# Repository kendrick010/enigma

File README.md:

# enigma

A 65% through-hole keyboard inspired by the Discipline V2 and Nibble keyboard.

The keyboard is flashed using QMK Toolbox.

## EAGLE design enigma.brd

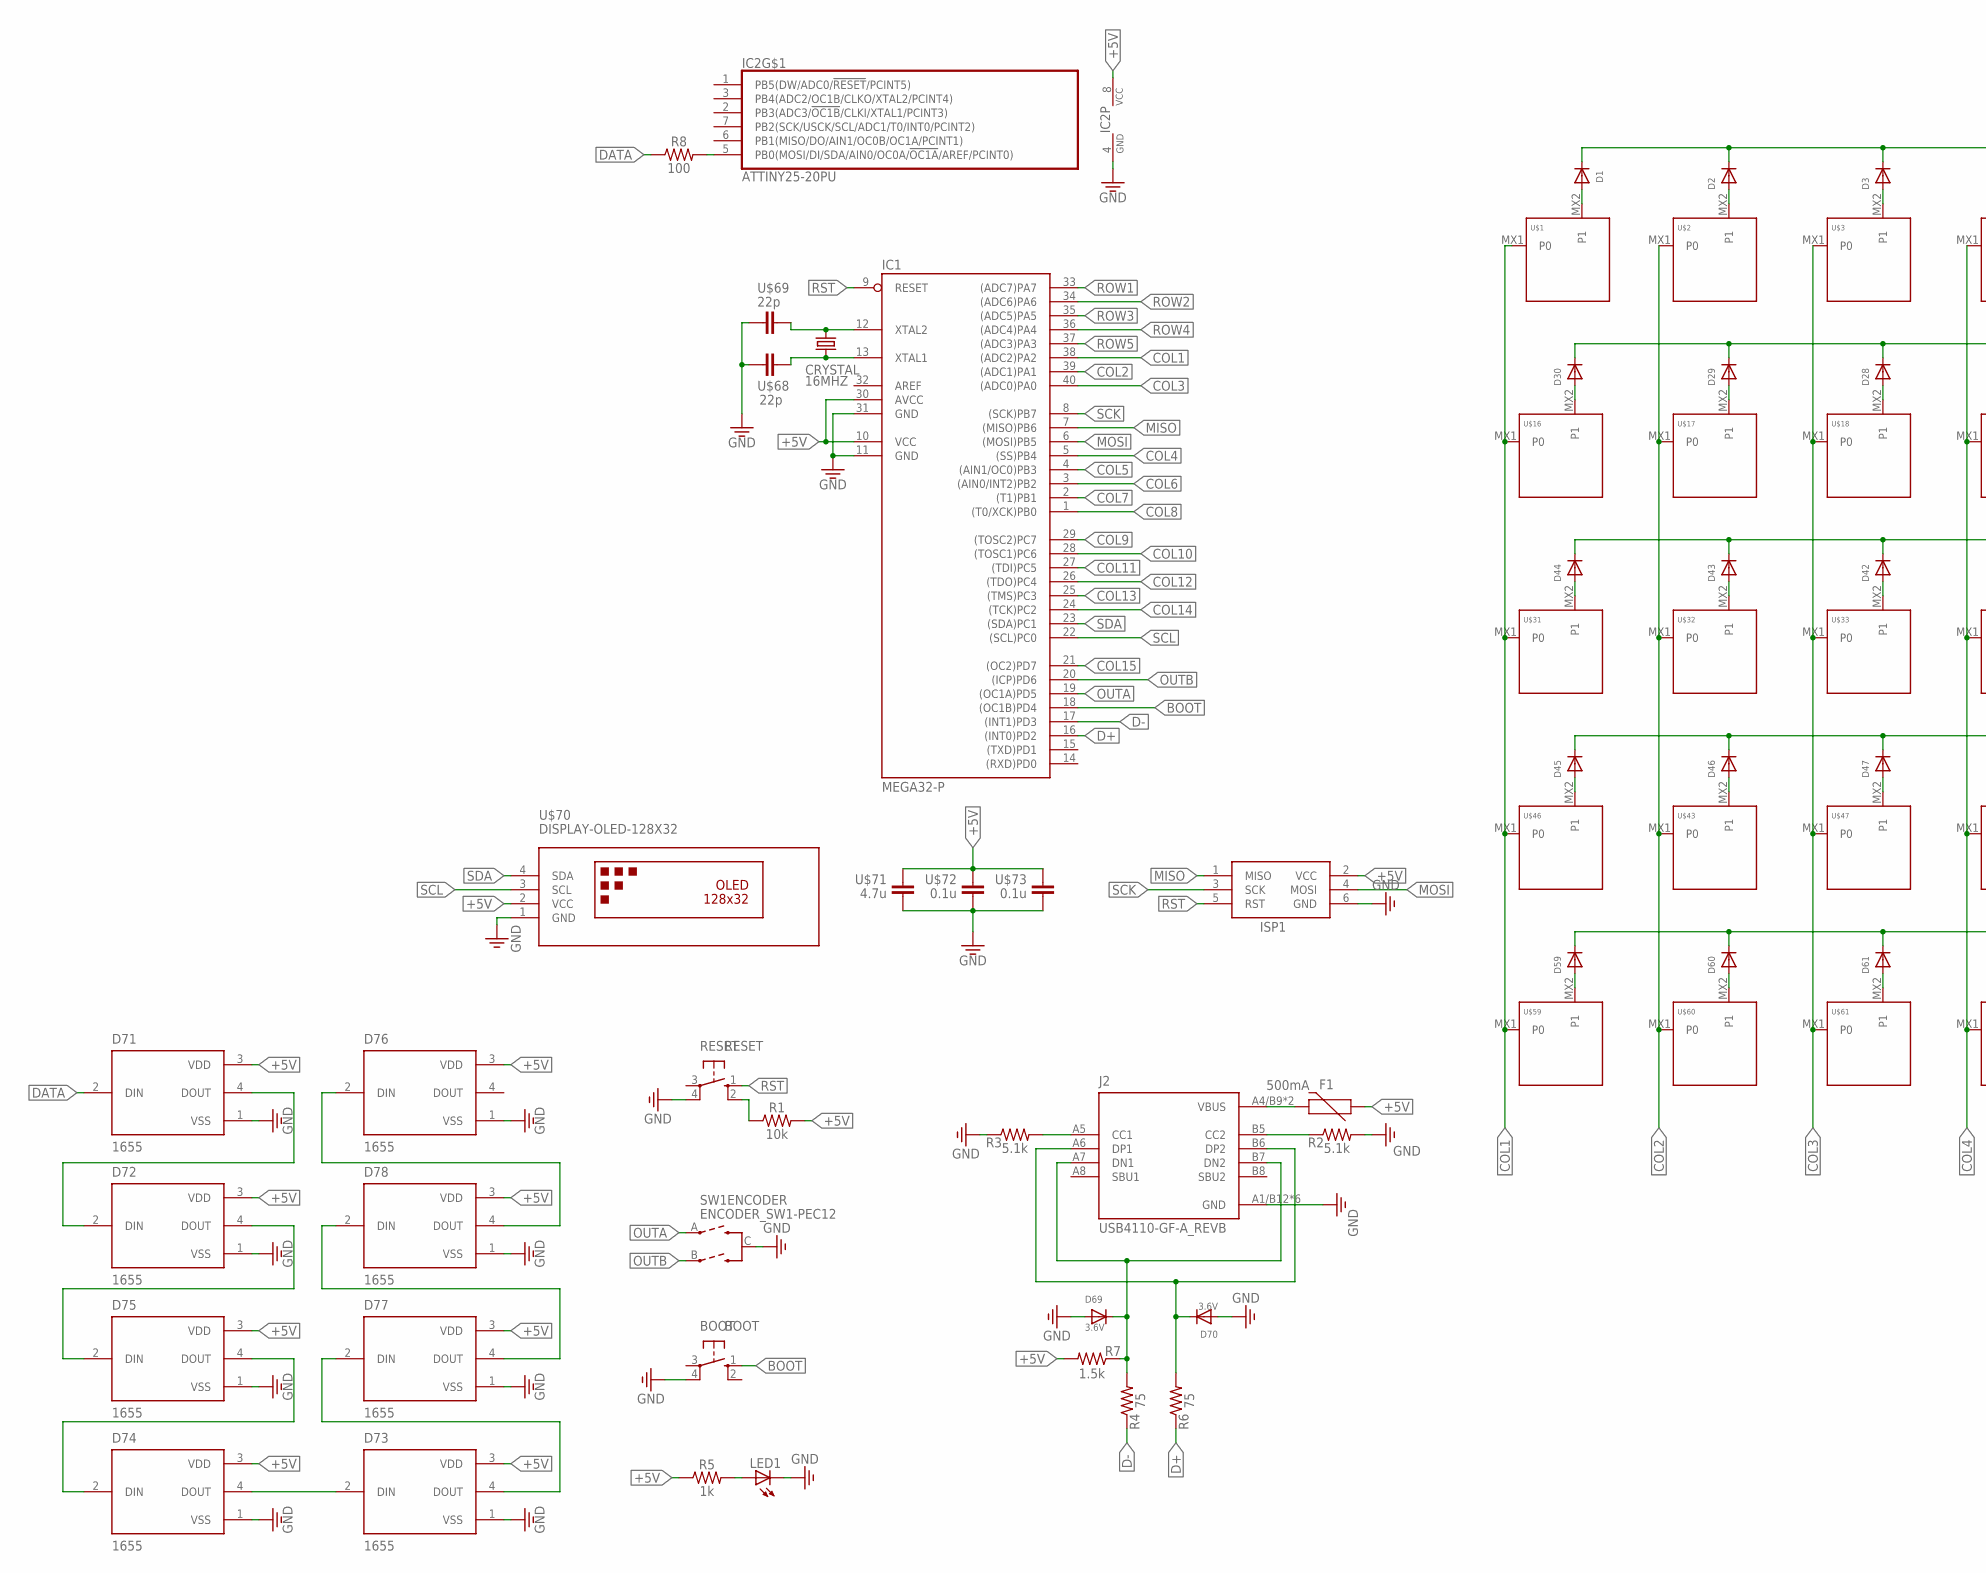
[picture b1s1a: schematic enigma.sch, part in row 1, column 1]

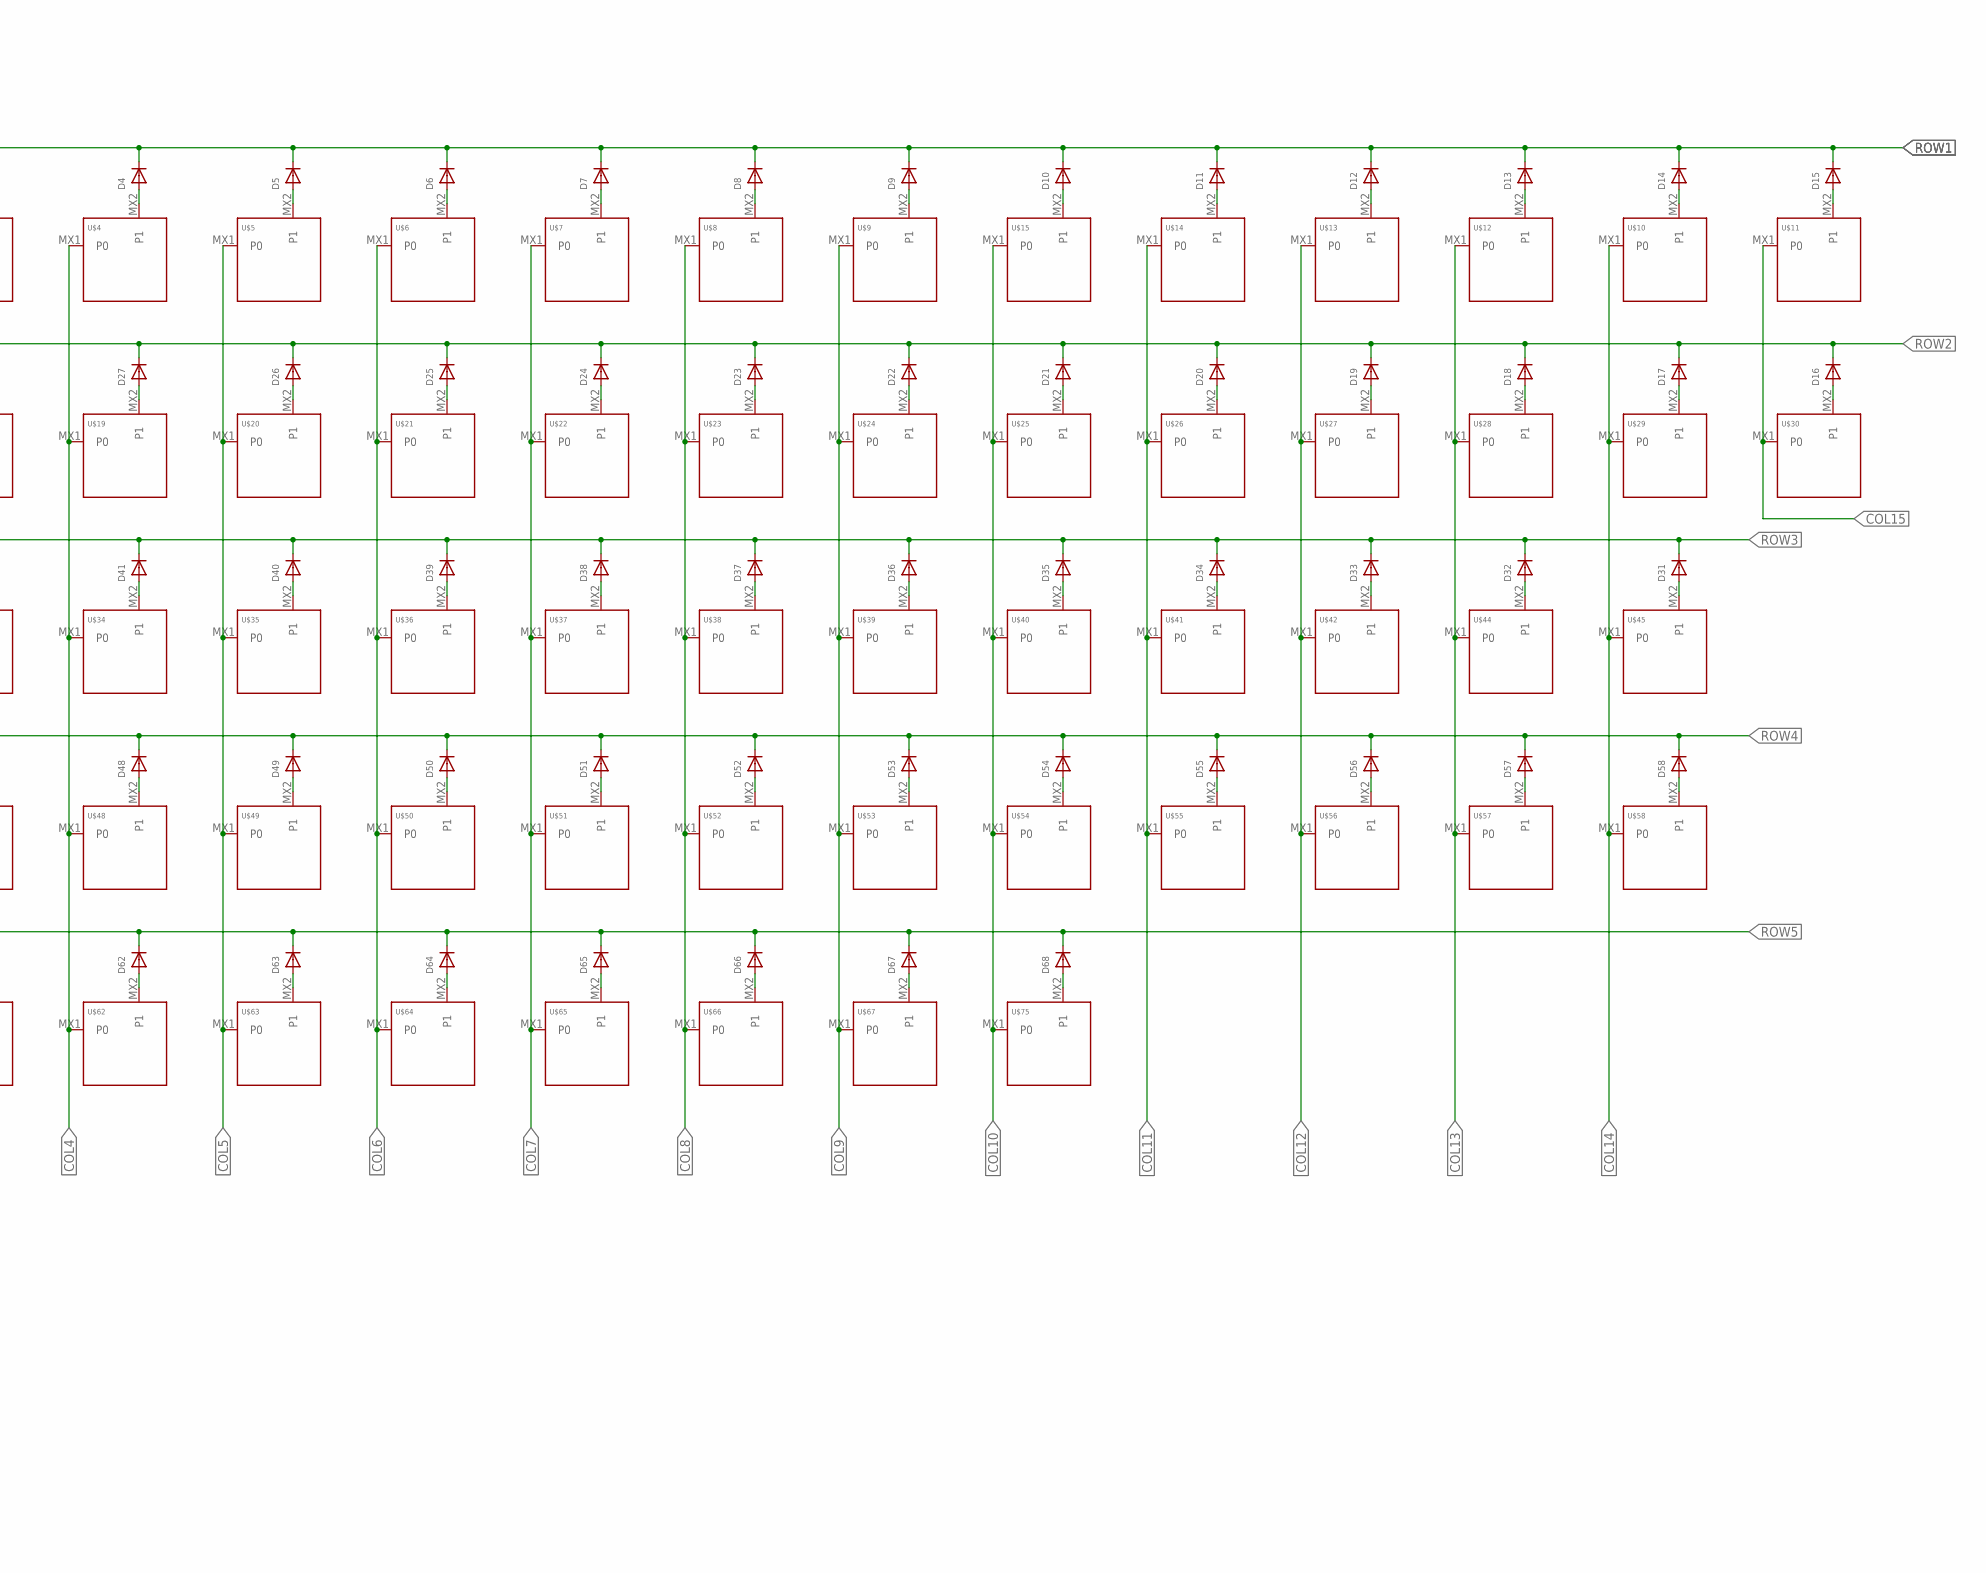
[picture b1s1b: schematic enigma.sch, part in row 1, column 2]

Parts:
BOOT: BOOT; B3F-10XX
CRYSTAL: 16MHZ; HC49U-V
D1, D2, D3, D4, D5, D6, D7, D8, D9, D10, D11, D12, D13, D14, D15, D16, D17, D18, D19, D20, D21, D22, D23, D24, D25, D26, D27, D28, D29, D30, D31, D32, D33, D34, D35, D36, D37, D38, D39, D40, D41, D42, D43, D44, D45, D46, D47, D48, D49, D50, D51, D52, D53, D54, D55, D56, D57, D58, D59, D60, D61, D62, D63, D64, D65, D66, D67, D68: DIODEDO-1N4148; DO-1N4148
D69, D70: 3.6V; DO-1N4148
D71, D72, D73, D74, D75, D76, D77, D78: 1655; LED_1655
F1: 500mA; PTH
IC1: MEGA32-P; DIL40
IC2: ATTINY25-20PU; DIL08
ISP1: AVRISP-6; AVRISP
J2: USB4110-GF-A_REVB; GCT_USB4110-GF-A_REVB
LED1: LED5MM
R1: 10k; AXIAL-0.3
R2, R3: 5.1k; AXIAL-0.3
R4, R6: 75; AXIAL-0.3
R5: 1k; AXIAL-0.3
R7: 1.5k; AXIAL-0.3
R8: 100; AXIAL-0.3
RESET: RESET; B3F-10XX
SW1: ENCODER_SW1-PEC12; PEC12_INCREMENTAL_ENCODER
U$1, U$2, U$3, U$4, U$5, U$6, U$7, U$8, U$9, U$11, U$12, U$13, U$14, U$15, U$16, U$17, U$18, U$19, U$20, U$21, U$22, U$23, U$24, U$25, U$26, U$27, U$28, U$29, U$30, U$31, U$32, U$33, U$34, U$35, U$36, U$37, U$38, U$39, U$40, U$41, U$42, U$43, U$45, U$47, U$48, U$49, U$50, U$51, U$52, U$53, U$54, U$55, U$56, U$57, U$58, U$59, U$60, U$61, U$63, U$64, U$65, U$66, U$67, U$75: KEYSWITCH-PLAIN-MXHSPCB-1U; MXHSPCB-1U
U$10: KEYSWITCH-PLAIN-MXHSPCB-2U; MXHSPCB-2U
U$44, U$46: KEYSWITCH-PLAIN-MXHSPCB-2U-FLIPPED; MXHSPCB-2U-FLIPPED
U$62: KEYSWITCH-PLAIN-MXHSPCB-6.25U-FLIPPED; MXHSPCB-6.25U-FLIPPED
U$68, U$69: 22p; CAP-TH
U$70: DISPLAY-OLED-128X32
U$71: 4.7u; CAP-TH
U$72, U$73: 0.1u; CAP-TH

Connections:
3.3V: BOOT.4 (P1), D69.A, D70.A, D71.1 (VSS), D72.1 (VSS), D73.1 (VSS), D74.1 (VSS), D75.1 (VSS), D76.1 (VSS), D77.1 (VSS), D78.1 (VSS), IC1.11 (GND), IC1.31 (GND), IC2.4 (GND), ISP1.6 (GND), J2.A1/B12 (GND), J2.B1/A12 (GND), J2.S1 (GND), J2.S2 (GND), J2.S3 (GND), J2.S4 (GND), LED1.K (C), R2.P$2 (2), R3.P$1 (1), RESET.4 (P1), SW1.C, U$68.2, U$69.1, U$70.1 (GND), U$71.1, U$72.1, U$73.1
+5V: D71.3 (VDD), D72.3 (VDD), D73.3 (VDD), D74.3 (VDD), D75.3 (VDD), D76.3 (VDD), D77.3 (VDD), D78.3 (VDD), F1.P$1 (1), IC1.10 (VCC), IC1.30 (AVCC), IC2.8 (VCC), ISP1.2 (VCC), R1.P$2 (2), R5.P$1 (1), R7.P$2 (2), U$70.2 (VCC), U$71.2, U$72.2, U$73.2
BOOT: BOOT.1 (S), IC1.18 ((OC1B)PD4)
COL1: IC1.38 ((ADC2)PA2), U$1.MX1 (P0), U$16.MX1 (P0), U$31.MX1 (P0), U$46.MX1 (P0), U$59.MX1 (P0)
COL2: IC1.39 ((ADC1)PA1), U$2.MX1 (P0), U$17.MX1 (P0), U$32.MX1 (P0), U$43.MX1 (P0), U$60.MX1 (P0)
COL3: IC1.40 ((ADC0)PA0), U$3.MX1 (P0), U$18.MX1 (P0), U$33.MX1 (P0), U$47.MX1 (P0), U$61.MX1 (P0)
COL4: IC1.5 ((SS)PB4), U$4.MX1 (P0), U$19.MX1 (P0), U$34.MX1 (P0), U$48.MX1 (P0), U$62.MX1 (P0)
COL5: IC1.4 ((AIN1/OC0)PB3), U$5.MX1 (P0), U$20.MX1 (P0), U$35.MX1 (P0), U$49.MX1 (P0), U$63.MX1 (P0)
COL6: IC1.3 ((AIN0/INT2)PB2), U$6.MX1 (P0), U$21.MX1 (P0), U$36.MX1 (P0), U$50.MX1 (P0), U$64.MX1 (P0)
COL7: IC1.2 ((T1)PB1), U$7.MX1 (P0), U$22.MX1 (P0), U$37.MX1 (P0), U$51.MX1 (P0), U$65.MX1 (P0)
COL8: IC1.1 ((T0/XCK)PB0), U$8.MX1 (P0), U$23.MX1 (P0), U$38.MX1 (P0), U$52.MX1 (P0), U$66.MX1 (P0)
COL9: IC1.29 ((TOSC2)PC7), U$9.MX1 (P0), U$24.MX1 (P0), U$39.MX1 (P0), U$53.MX1 (P0), U$67.MX1 (P0)
COL10: IC1.28 ((TOSC1)PC6), U$15.MX1 (P0), U$25.MX1 (P0), U$40.MX1 (P0), U$54.MX1 (P0), U$75.MX1 (P0)
COL11: IC1.27 ((TDI)PC5), U$14.MX1 (P0), U$26.MX1 (P0), U$41.MX1 (P0), U$55.MX1 (P0)
COL12: IC1.26 ((TDO)PC4), U$13.MX1 (P0), U$27.MX1 (P0), U$42.MX1 (P0), U$56.MX1 (P0)
COL13: IC1.25 ((TMS)PC3), U$12.MX1 (P0), U$28.MX1 (P0), U$44.MX1 (P0), U$57.MX1 (P0)
COL14: IC1.24 ((TCK)PC2), U$10.MX1 (P0), U$29.MX1 (P0), U$45.MX1 (P0), U$58.MX1 (P0)
COL15: IC1.21 ((OC2)PD7), U$11.MX1 (P0), U$30.MX1 (P0)
D+: IC1.16 ((INT0)PD2), R6.P$1 (1)
D-: IC1.17 ((INT1)PD3), R4.P$1 (1)
DATA: D71.2 (DIN), R8.P$1 (1)
MISO: IC1.7 ((MISO)PB6), ISP1.1 (MISO)
MOSI: IC1.6 ((MOSI)PB5), ISP1.4 (MOSI)
unnamed: D1.A, U$1.MX2 (P1)
unnamed: D2.A, U$2.MX2 (P1)
unnamed: D3.A, U$3.MX2 (P1)
unnamed: D4.A, U$4.MX2 (P1)
unnamed: D5.A, U$5.MX2 (P1)
unnamed: D6.A, U$6.MX2 (P1)
unnamed: D7.A, U$7.MX2 (P1)
unnamed: D8.A, U$8.MX2 (P1)
unnamed: D9.A, U$9.MX2 (P1)
unnamed: D10.A, U$15.MX2 (P1)
unnamed: D11.A, U$14.MX2 (P1)
unnamed: D12.A, U$13.MX2 (P1)
unnamed: D13.A, U$12.MX2 (P1)
unnamed: D14.A, U$10.MX2 (P1)
unnamed: D15.A, U$11.MX2 (P1)
unnamed: D30.A, U$16.MX2 (P1)
unnamed: D29.A, U$17.MX2 (P1)
unnamed: D28.A, U$18.MX2 (P1)
unnamed: D27.A, U$19.MX2 (P1)
unnamed: D26.A, U$20.MX2 (P1)
unnamed: D25.A, U$21.MX2 (P1)
unnamed: D24.A, U$22.MX2 (P1)
unnamed: D23.A, U$23.MX2 (P1)
unnamed: D22.A, U$24.MX2 (P1)
unnamed: D21.A, U$25.MX2 (P1)
unnamed: D20.A, U$26.MX2 (P1)
unnamed: D19.A, U$27.MX2 (P1)
unnamed: D18.A, U$28.MX2 (P1)
unnamed: D17.A, U$29.MX2 (P1)
unnamed: D16.A, U$30.MX2 (P1)
unnamed: D44.A, U$31.MX2 (P1)
unnamed: D43.A, U$32.MX2 (P1)
unnamed: D42.A, U$33.MX2 (P1)
unnamed: D41.A, U$34.MX2 (P1)
unnamed: D40.A, U$35.MX2 (P1)
unnamed: D39.A, U$36.MX2 (P1)
unnamed: D38.A, U$37.MX2 (P1)
unnamed: D37.A, U$38.MX2 (P1)
unnamed: D36.A, U$39.MX2 (P1)
unnamed: D35.A, U$40.MX2 (P1)
unnamed: D34.A, U$41.MX2 (P1)
unnamed: D33.A, U$42.MX2 (P1)
unnamed: D32.A, U$44.MX2 (P1)
unnamed: D31.A, U$45.MX2 (P1)
unnamed: D45.A, U$46.MX2 (P1)
unnamed: D46.A, U$43.MX2 (P1)
unnamed: D47.A, U$47.MX2 (P1)
unnamed: D48.A, U$48.MX2 (P1)
unnamed: D49.A, U$49.MX2 (P1)
unnamed: D50.A, U$50.MX2 (P1)
unnamed: D51.A, U$51.MX2 (P1)
unnamed: D52.A, U$52.MX2 (P1)
unnamed: D53.A, U$53.MX2 (P1)
unnamed: D54.A, U$54.MX2 (P1)
unnamed: D55.A, U$55.MX2 (P1)
unnamed: D56.A, U$56.MX2 (P1)
unnamed: D57.A, U$57.MX2 (P1)
unnamed: D58.A, U$58.MX2 (P1)
unnamed: D67.A, U$67.MX2 (P1)
unnamed: D66.A, U$66.MX2 (P1)
unnamed: D65.A, U$65.MX2 (P1)
unnamed: D64.A, U$64.MX2 (P1)
unnamed: D63.A, U$63.MX2 (P1)
unnamed: D62.A, U$62.MX2 (P1)
unnamed: D61.A, U$61.MX2 (P1)
unnamed: D60.A, U$60.MX2 (P1)
unnamed: D68.A, U$75.MX2 (P1)
unnamed: CRYSTAL.1, IC1.12 (XTAL2), U$69.2
unnamed: CRYSTAL.2, IC1.13 (XTAL1), U$68.1
unnamed: D59.A, U$59.MX2 (P1)
unnamed: F1.P$2 (2), J2.A4/B9 (VBUS), J2.B4/A9 (VBUS)
unnamed: J2.B5 (CC2), R2.P$1 (1)
unnamed: J2.A5 (CC1), R3.P$2 (2)
unnamed: D69.C, J2.A7 (DN1), J2.B7 (DN2), R4.P$2 (2), R7.P$1 (1)
unnamed: LED1.A, R5.P$2 (2)
unnamed: R1.P$1 (1), RESET.2 (S1)
unnamed: IC2.5 (PB0(MOSI/DI/SDA/AIN0/OC0A/!OC1A!/AREF/P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), R8.P$2 (2)
unnamed: D71.4 (DOUT), D72.2 (DIN)
unnamed: D70.C, J2.A6 (DP1), J2.B6 (DP2), R6.P$2 (2)
unnamed: D72.4 (DOUT), D75.2 (DIN)
unnamed: D74.2 (DIN), D75.4 (DOUT)
unnamed: D73.2 (DIN), D74.4 (DOUT)
unnamed: D73.4 (DOUT), D77.2 (DIN)
unnamed: D77.4 (DOUT), D78.2 (DIN)
unnamed: D76.2 (DIN), D78.4 (DOUT)
OUTA: IC1.19 ((OC1A)PD5), SW1.A
OUTB: IC1.20 ((ICP)PD6), SW1.B
ROW1: D1.C, D2.C, D3.C, D4.C, D5.C, D6.C, D7.C, D8.C, D9.C, D10.C, D11.C, D12.C, D13.C, D14.C, D15.C, IC1.33 ((ADC7)PA7)
ROW2: D16.C, D17.C, D18.C, D19.C, D20.C, D21.C, D22.C, D23.C, D24.C, D25.C, D26.C, D27.C, D28.C, D29.C, D30.C, IC1.34 ((ADC6)PA6)
ROW3: D31.C, D32.C, D33.C, D34.C, D35.C, D36.C, D37.C, D38.C, D39.C, D40.C, D41.C, D42.C, D43.C, D44.C, IC1.35 ((ADC5)PA5)
ROW4: D45.C, D46.C, D47.C, D48.C, D49.C, D50.C, D51.C, D52.C, D53.C, D54.C, D55.C, D56.C, D57.C, D58.C, IC1.36 ((ADC4)PA4)
ROW5: D59.C, D60.C, D61.C, D62.C, D63.C, D64.C, D65.C, D66.C, D67.C, D68.C, IC1.37 ((ADC3)PA3)
RST: IC1.9 (RESET), ISP1.5 (RST), RESET.1 (S)
SCK: IC1.8 ((SCK)PB7), ISP1.3 (SCK)
SCL: IC1.22 ((SCL)PC0), U$70.3 (SCL)
SDA: IC1.23 ((SDA)PC1), U$70.4 (SDA)

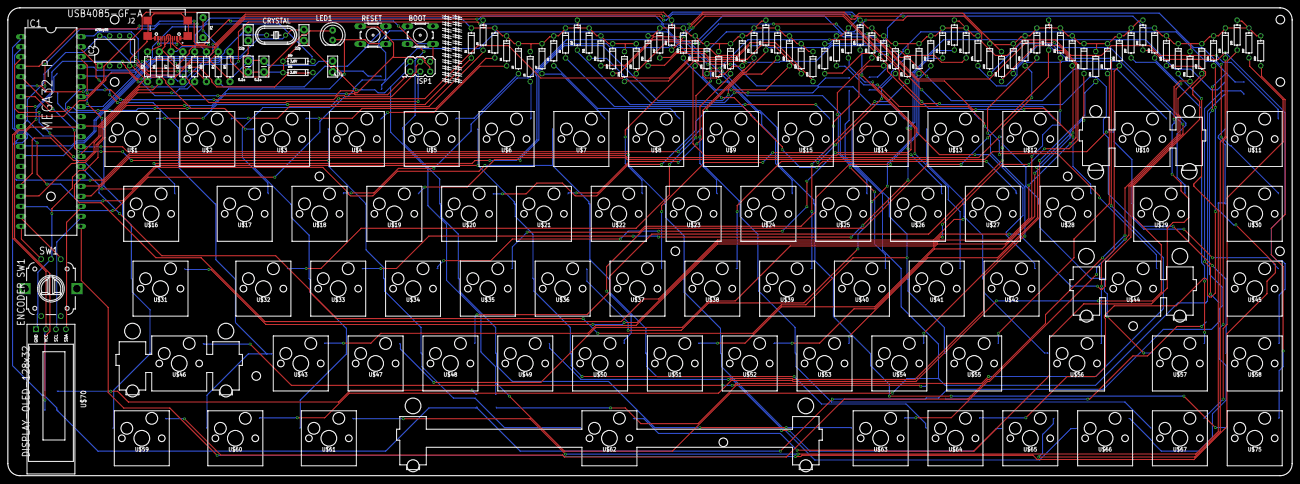
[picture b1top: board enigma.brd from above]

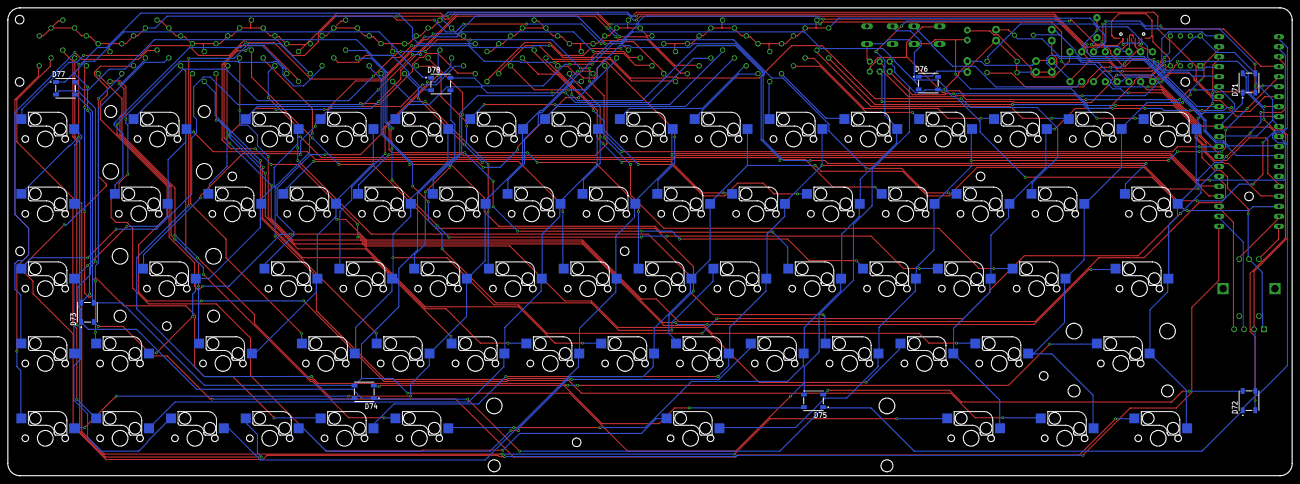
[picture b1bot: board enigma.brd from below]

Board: 2 copper layers, 327.0 x 119.1 mm, 170 parts (76 on the bottom side), 119 nets.

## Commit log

2021-10-31 enigma qmk firmware
2021-10-31 fixing .gitignore
2021-10-31 enigma firmware
2021-10-31 .DS_Store removed
2021-10-31 enigma extra
2021-12-23 ATtiny code
2021-12-23 new keymaps

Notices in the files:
parts and their libraries:
SparkFun-Fuses: Licensing: Creative Commons ShareAlike 4.0 International - https://creativecommons.org/licenses/by-sa/4.0
diy-modules: Released under the Creative Commons Attribution 4.0 International License: http://creativecommons.org/licenses/by/4.0
